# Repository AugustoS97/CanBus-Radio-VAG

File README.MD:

# CAN BUS interface for powering up the DSP/Sound System Amplifier for SKODA, VOLKSWAGEN, AUDI AND SEAT vehicules with non original radios

System for switching on original speakers amplifier and DSP with CAN BUS control.

Tested in a Skoda Octavia 1Z (year 2005) Edition 100 with Audience radio (6-CD changer included) and 12-speaker Sound system with active DSP controlled by CAN BUS (model 1Z0 035 456).

")

## Solution provided

A CAN controller has been developed using an ATMega 328P microcontroller (Arduino) and the CAN BUS MCP2515 interface with a TJA1050T transceiver. It allows direct power supply to the vehicle voltage (up to 20V) thanks to the MP2307 DC/DC regulator.

This interface enables the following functions:
- Switching on the sound/amplifier controller, active equaliser or DSP of a VAG group vehicle.
- Getting a 12V signal when the vehicle's ignition is switched on (work in progress).
- Getting a 12V signal when the reverse gear is engaged (work in progress).
- Control a fan to cool the vehicle radio when the vehicle radio is on.
- Getting a signal from the steering wheel controls to integrate them into a conventional radio (work in progress).

### Prototipe

### Final solution

The PCB designed has a JST XH 2.54 connector with 8 pins to connect to the radio and car wires. Also the interface has a ICSP and Serial connection to program and debug.

#### Electronic eschema

The connection eschema and PCB design is the following:

#### PCB Designed

The 3D model of the PCB is as follow:

### Working in vehicule

It has been tested in my Skoda Octavia with an Android chineese radio, and using the module developed it is possible to use the original amplifier with the original soundsystem. Without this CAN Controller it is not possible to power on the DSP, so is impossible to get sound by the speakers. 

Here is possible to see some pictures of the process:

- Work in progress.

## In-vehicle wiring diagram with any radio

The connection to the module must be made as follows:

- 12V in, must be connected to an ignition after contact or to the AMP REMOTE pin of the radio, so that the module is only activated when the radio is switched on.
- GND, must be connected to the vehicle chassis or to a GND of the radio.
- CAN H, must be connected to the CAN HIGH pin of the vehicle (on the FAKRA connector)
- CAN L, must be connected to the vehicle's CAN LOW pin (on the FAKRA connector)
- Mult1 and Mult 2, are reverse and ignition signals (development in progress).

## Software requirements

To load the code on the developed board, an ISP programmer and the Arduino IDE must be used.
- The libraries required for the project are as follows:
  - [CAN Shield library](https://github.com/coryjfowler/MCP_CAN_lib)

## BOM for PCB

It is possible to find the BOM with the LCSC reference [here](/Electronic/PCB/CanBus-Radio-VAG-V1.0/ASSEMBLY/CanBus-Radio-VAG-V1.0-BOM.xlsx).

Also, the GERBER file for one PCB and for a panel (panelizing the order, you can reduce the cost) is available [here](/Electronic/PCB/CanBus-Radio-VAG-V1.0/GERBER/CanBus-Radio-VAG-V1-Gerber.zip).

## Extra functions

To activate the front sensors from the vehicle's parking button, the power pin of the parking button connector must be connected to the reverse signal from the camera. It is recommended that a 1N4007 diode is used to prevent current flowing back to the button from the radio or from the button to the CAN BUS module.

Here you can see an scheme of this connection.

## Buy the CAN Controller

If you want to buy a CAN Controller to enable your DSP and use the original sound system with non-stock radios in Volkswagen, Audi, Skoda and Seat, you can contact with me by email (augustosamuelhdezmartin@gmail.com) or you can buy it in E-bay here.

## Other tools

Also there is a [folder](/Arduino/tools/CanHacker/) with the CAN HACKER software and the code to upload to Arduino to use a MCP2515 module + Arduino Nano as a CAN BUS sniffer and get all the message in the PC using the CAN HACKER software. With this method I could find the radio messages, so I could create this CAN BUS interface.

## Links of interest

Some interesting links:

- [A way to use stock amp with after market radio SKODA](https://www.briskoda.net/forums/topic/449813-solved-better-way-of-using-stock-amp-with-after-market-radio/#comment-5463635)
- [How to use after market radio with the stock amplifier in SKODA, SEAT, VOLKSWAGEN and AUDI cars](https://www.briskoda.net/forums/topic/378504-solved-how-to-use-stock-amplifier-with-after-market-hu/)

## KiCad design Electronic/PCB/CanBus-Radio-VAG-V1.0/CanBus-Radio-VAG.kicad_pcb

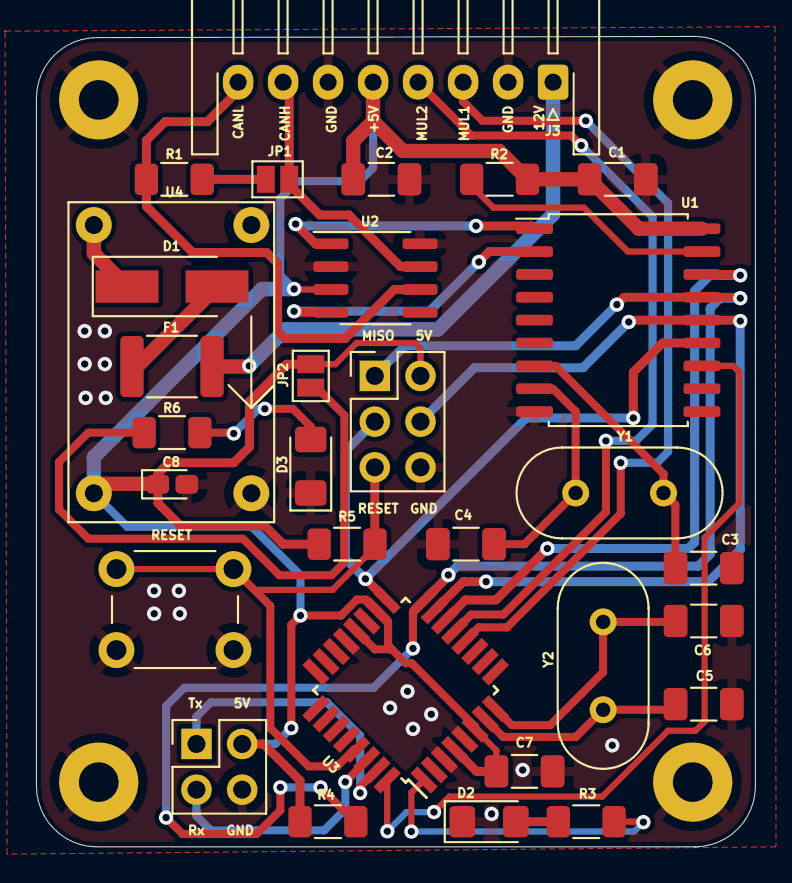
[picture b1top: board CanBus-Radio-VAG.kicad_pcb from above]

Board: 2 copper layers, 39.9 x 45.0 mm, 34 parts (0 on the bottom side), 29 nets.

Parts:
C1, C2: 100n; C_1206_3216Metric_Pad1.33x1.80mm_HandSolder
C3, C4: 27pF; C_1206_3216Metric_Pad1.33x1.80mm_HandSolder
C5: 12-22 pF; C_1206_3216Metric_Pad1.33x1.80mm_HandSolder
C6: 12-22pF; C_1206_3216Metric_Pad1.33x1.80mm_HandSolder
C7: 100nF; C_1206_3216Metric_Pad1.33x1.80mm_HandSolder
C8: 1uF; CP_EIA-1608-10_AVX-L_Pad1.25x1.05mm_HandSolder
D1: 1N4007; D_SMA_Handsoldering
D2, D3: LED; LED_1206_3216Metric_Pad1.42x1.75mm_HandSolder
F1: fuse 1A; Fuse_1812_4532Metric_Pad1.30x3.40mm_HandSolder
H1, H2, H3, H4: MountingHole; MountingHole_2.2mm_M2_Pad
J1: UART; PinHeader_2x02_P2.54mm_Vertical
J2: ICSP; PinHeader_2x03_P2.54mm_Vertical
J3: CAR; JST_XH_S8B-XH-A-1_1x08_P2.50mm_Horizontal
JP1: CAN-TERM-JUMPER; SolderJumper-2_P1.3mm_Open_Pad1.0x1.5mm
JP2: ON-LED; SolderJumper-2_P1.3mm_Open_Pad1.0x1.5mm
R1: 120R; R_1206_3216Metric_Pad1.30x1.75mm_HandSolder
R2: 10k; R_1206_3216Metric_Pad1.30x1.75mm_HandSolder
R3, R6: 10K; R_1206_3216Metric_Pad1.30x1.75mm_HandSolder
R4: 5k; R_1206_3216Metric_Pad1.30x1.75mm_HandSolder
R5: 1k; R_1206_3216Metric_Pad1.30x1.75mm_HandSolder
SW1: SW_Push-Switch; SW_PUSH_6mm_H5mm
U1: MCP2515-xSO; SOIC-18W_7.5x11.6mm_P1.27mm
U2: TJA1050T; SOIC-8_3.9x4.9mm_P1.27mm
U3: ATmega328P-PU; TQFP-32_7x7mm_P0.8mm
U4: MP2307
Y1: 8MHz; Crystal_HC49-4H_Vertical
Y2: 16MHz; Crystal_HC49-4H_Vertical

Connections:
+5V: C1.1, C2.1, C7.1, C8.1, J1.2, J2.2, J3.5, JP2.1, R2.1, R4.1, R5.1, U1.18, U2.3, U3.4, U3.6, U3.18, U3.20, U4.3
+12V: F1.1, J3.1
/MISO: J2.1, R4.2, U1.15, U3.16
/MOSI: J2.4, U1.14, U3.15
/MULT_1: J3.3, U3.12
/MULT_2: J3.4, U3.13
/RESET: J2.5, R5.2, SW1.1, U3.29
/SCK: J2.3, U1.13, U3.17
/SS_MCP: U1.16, U3.14
CANH: J3.7, JP1.1, U2.7
CANL: J3.8, R1.2, U2.6
GND: C1.2, C2.2, C3.2, C4.2, C5.2, C6.2, C7.2, C8.2, D2.1, D3.1, H1.1, H2.1, H3.1, H4.1, J1.4, J2.6, J3.2, J3.6, SW1.2, U1.9, U2.2, U2.8, U3.3, U3.5, U3.21, U4.2, U4.4
MCP_INT: U1.12, U3.32
unnamed: C3.1, U1.7, Y1.1
unnamed: C4.1, U1.8, Y1.2
unnamed: C5.1, U3.7, Y2.2
unnamed: C6.1, U3.8, Y2.1
unnamed: D1.1, U4.1
unnamed: D1.2, F1.2
unnamed: D2.2, R3.2
unnamed: D3.2, R6.2
unnamed: JP1.2, R1.1
unnamed: JP2.2, R6.1
unnamed: R2.2, U1.17
unnamed: R3.1, U3.1
RX: J1.3, U3.30
RXCAN: U1.2, U2.4
TX: J1.1, U3.31
TXCAN: U1.1, U2.1

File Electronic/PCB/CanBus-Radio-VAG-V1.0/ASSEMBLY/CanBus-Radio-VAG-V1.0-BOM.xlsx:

| Columna2 | Columna3 | Columna1 | Columna4
Comment | Designator | Footprint | LCSC Part Number | Qnty
100n | C1, C2, | Capacitor_SMD:C_1206_3216Metric_Pad1.33x1.80mm_HandSolder | C840121 | 2
27pF | C3, C4, | Capacitor_SMD:C_1206_3216Metric_Pad1.33x1.80mm_HandSolder | C1899 | 2
22pF | C5, | Capacitor_SMD:C_1206_3216Metric_Pad1.33x1.80mm_HandSolder | C565687 | 1
22pF | C6, | Capacitor_SMD:C_1206_3216Metric_Pad1.33x1.80mm_HandSolder | C565687 | 1
100nF | C7, | Capacitor_SMD:C_1206_3216Metric_Pad1.33x1.80mm_HandSolder | C840121 | 1
1uF | C8, | Capacitor_Tantalum_SMD:CP_EIA-1608-10_AVX-L_Pad1.25x1.05mm_HandSolder | C307912 | 1
1N4007 | D1, | Diode_SMD:D_SMA_Handsoldering | C2909831 | 1
LED | D2, D3, | LED_SMD:LED_1206_3216Metric_Pad1.42x1.75mm_HandSolder | C375458 | 2
fuse 1A | F1, | Fuse:Fuse_1812_4532Metric_Pad1.30x3.40mm_HandSolder | C151169 | 1
UART | J1, | Connector_PinHeader_2.54mm:PinHeader_2x02_P2.54mm_Vertical | C706892 | 1
ICSP | J2, | Connector_PinHeader_2.54mm:PinHeader_2x03_P2.54mm_Vertical | C706893 | 1
CAR | J3, | Connector_JST:JST_XH_S8B-XH-A-1_1x08_P2.50mm_Horizontal |  | 1
120R | R1, | Resistor_SMD:R_1206_3216Metric_Pad1.30x1.75mm_HandSolder | C114928 | 1
10k | R2, | Resistor_SMD:R_1206_3216Metric_Pad1.30x1.75mm_HandSolder | C3018037 | 1
10K | R3, R6, | Resistor_SMD:R_1206_3216Metric_Pad1.30x1.75mm_HandSolder | C3018037 | 2
5k | R4, | Resistor_SMD:R_1206_3216Metric_Pad1.30x1.75mm_HandSolder | C136458 | 1
1k | R5, | Resistor_SMD:R_1206_3216Metric_Pad1.30x1.75mm_HandSolder | C408770 | 1
SW_Push-Switch | SW1, | Button_Switch_THT:SW_PUSH_6mm_H5mm | C2828578 | 1
MCP2515-xSO | U1, | Package_SO:SOIC-18W_7.5x11.6mm_P1.27mm | C12368 | 1
TJA1050T | U2, | Package_SO:SOIC-8_3.9x4.9mm_P1.27mm | C6952 | 1
ATmega328P-PU | U3, | SmartBMS:TQFP-32_7x7mm_P0.8mm | C14877 | 1
8MHz | Y1, | Crystal:Crystal_HC49-4H_Vertical | C655216 | 1
16MHz | Y2, | Crystal:Crystal_HC49-4H_Vertical | C390745 | 1

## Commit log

2023-01-14 Added first design.
2023-01-16 Added some tools and the panelize design.
2023-01-17 Changes in the README file
2023-01-17 README update
2023-01-17 Some changes in code
2023-02-06 Some minor changes
2023-02-11 Some changes in code.
2023-02-13 Case design add
